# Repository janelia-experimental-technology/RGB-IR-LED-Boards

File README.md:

# RGB-IR-LED-Boards
 RGB-IR backlights 
Various LED boards that provide color and IR lighting (primarily for backlighting) in steady or pulsed modes. 
The boards are controlled by a USB-Serial command interface that provides a wide variety of opearting modes.
The 5x5 single color and RGB Combined Color have been depracated and are for reference only. 
The cuurent boards have LED areas of 5" x 5" or 7" x 7" and use separate LEDs for each color, allowing up to
three colors to be used on one board (in addition to IR). The firmware and command interace is common to all 
boards, though some features may not be available on all boards.

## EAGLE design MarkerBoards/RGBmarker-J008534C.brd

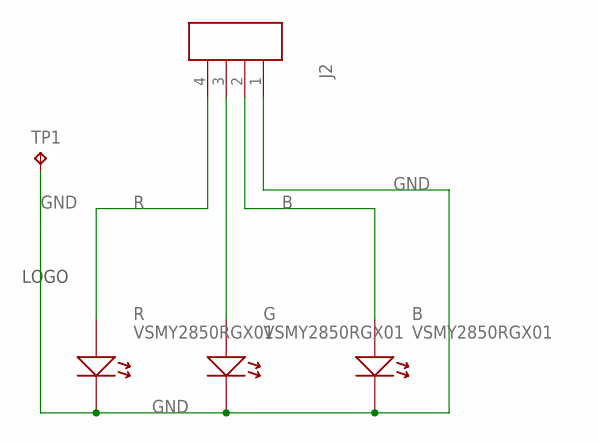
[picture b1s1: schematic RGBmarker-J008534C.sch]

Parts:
B: VSMY2850RGX01; LED_THRU_VSMY
G: VSMY2850RGX01; LED_THRU_VSMY
J2: CON4533980471; 533980471
R: VSMY2850RGX01; LED_THRU_VSMY
TP1: TPB1,27; B1,27
U$1: JFRC-LOGOLOGO_OP; LOGO_BMP_OP

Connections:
B: B.A, J2.2
GND: B.C (K), G.C (K), J2.1, R.C (K), TP1.TP
unnamed: G.A, J2.3
R: J2.4, R.A

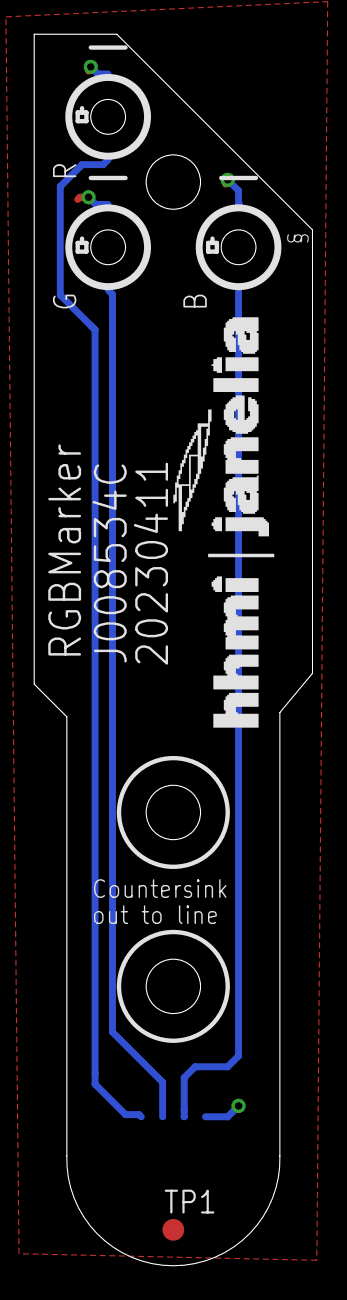
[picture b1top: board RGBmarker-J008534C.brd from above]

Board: 2 copper layers, 16.3 x 71.9 mm, 6 parts (1 on the bottom side), 4 nets.

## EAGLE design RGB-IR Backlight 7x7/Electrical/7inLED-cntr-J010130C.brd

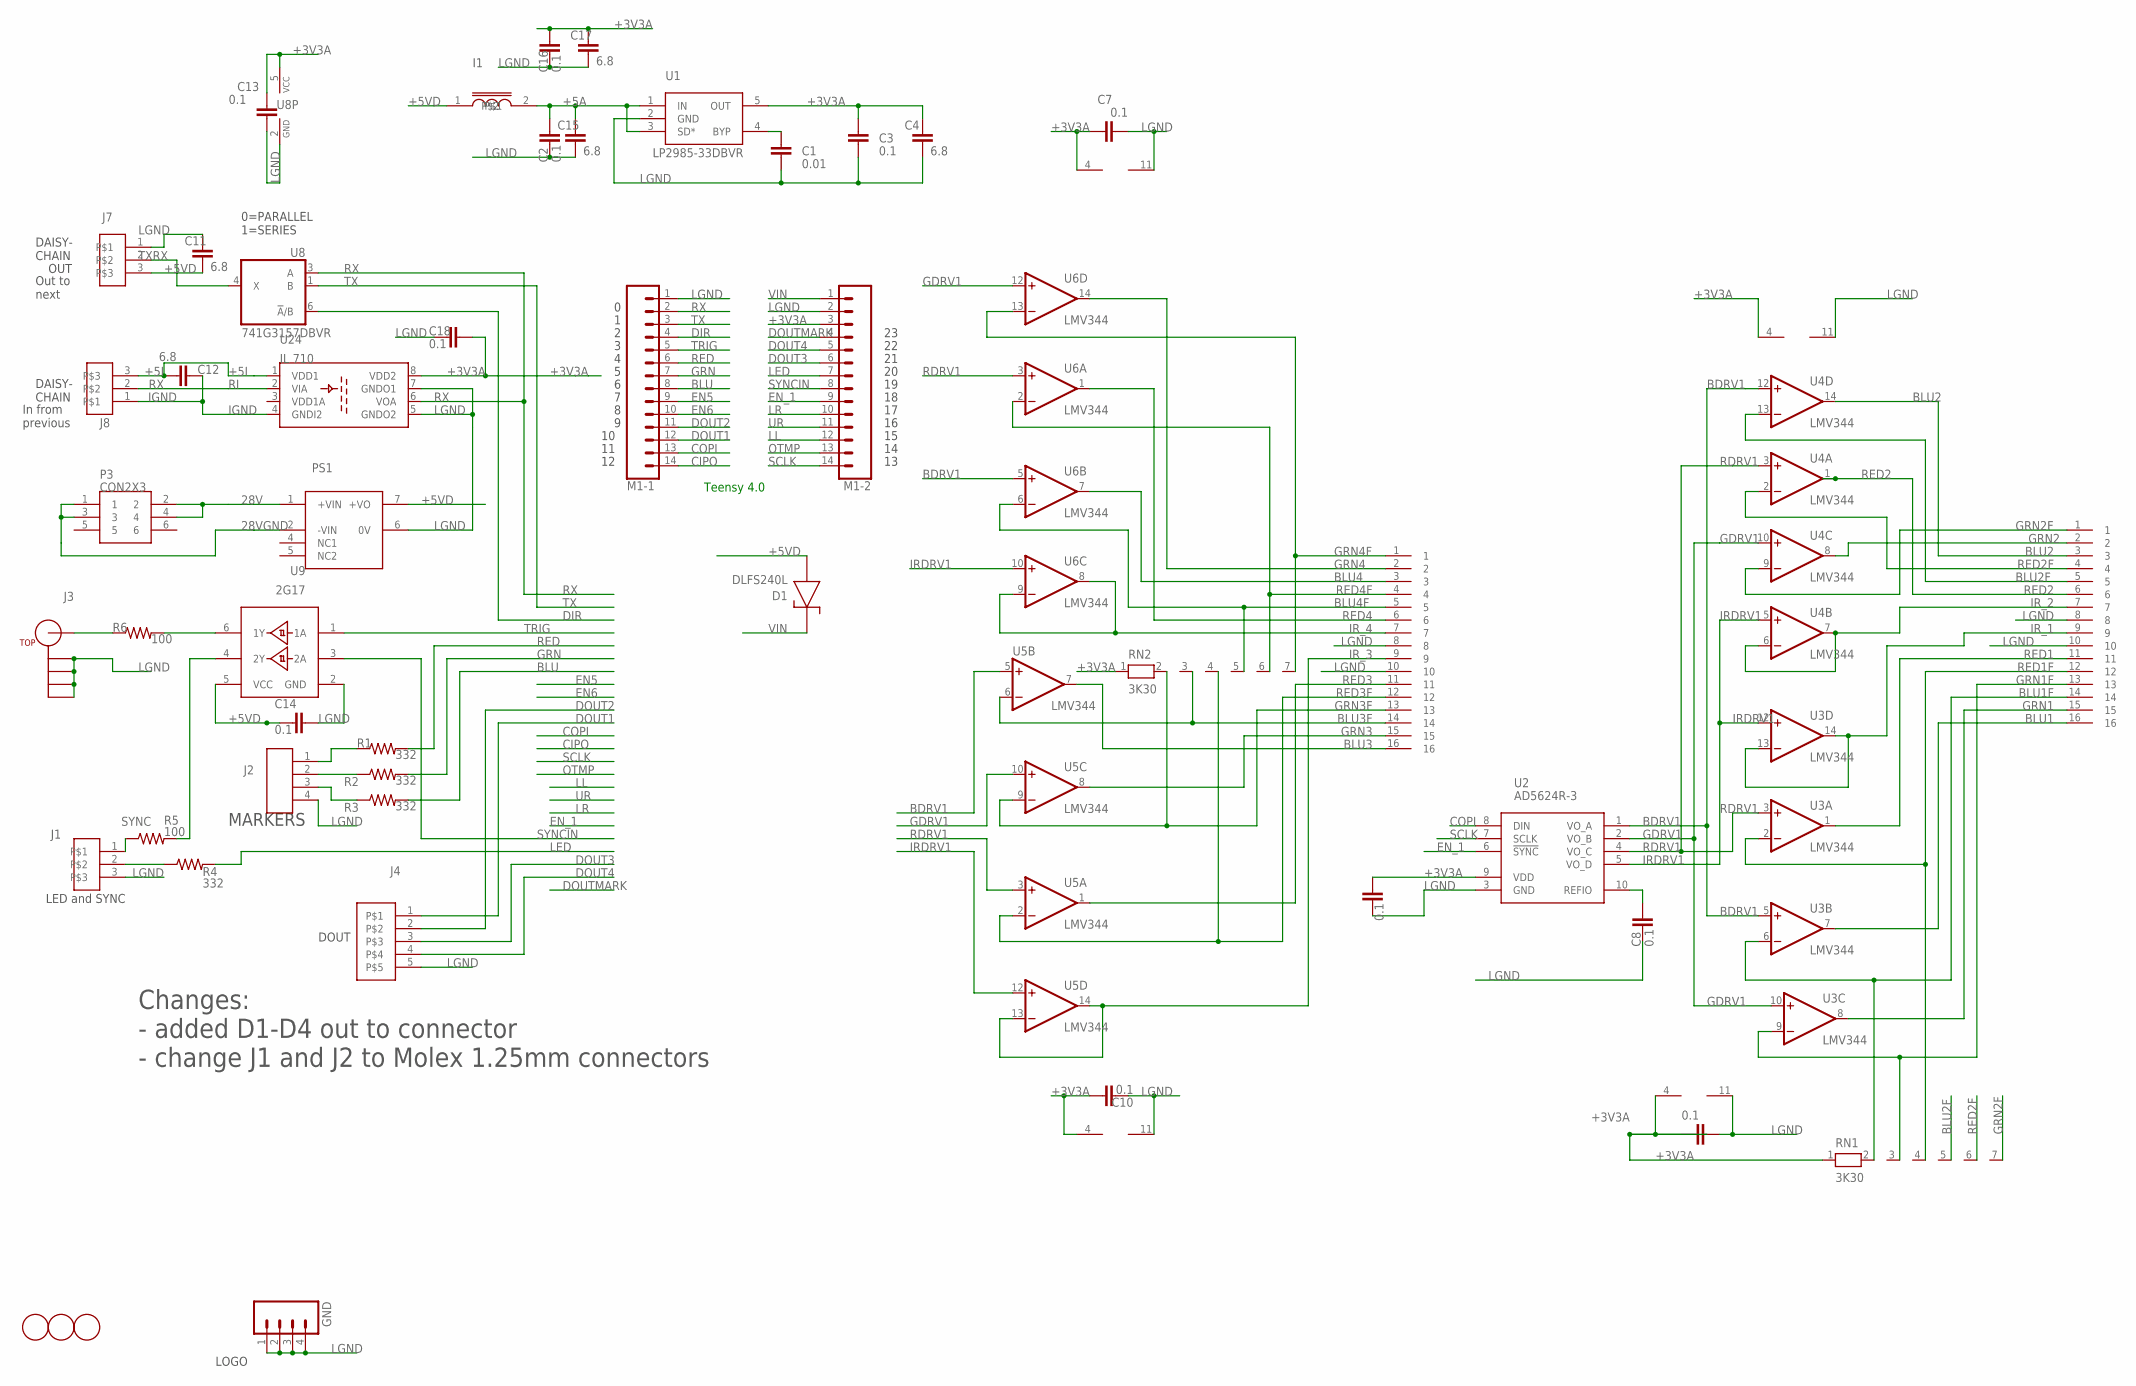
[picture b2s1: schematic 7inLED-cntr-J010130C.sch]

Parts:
C1: 0.01; 0805S
C2, C3, C5, C7, C8, C9, C10, C13, C14, C16, C18: 0.1; 0603S
C4, C15, C17: 6.8; 1206S
C11, C12: 6.8; 1210S
D1: DLFS240L; PWRDI-123
FID1, FID2, FID3: FIDUCIAL; FIDUCIAL_1MM
GND: M04LOCK; 1X04_LOCK
I1: INDUCTOR0805S; 0805S
J1: CON3DF13-3TH; DF13-3P-TH
J2: CON4DF13-4-TH; DF13-4-TH
J3: BNC-4PADBNC-5-1634503-1; 5-1634503-1
J4: CON5AMPMODU-5; AMPMODU-5
J7, J8: CON3AMPMODU-3; AMPMODU-3
M1-1, M1-2: CONN_14; 1X14
P1, P2: CON162X8PLUG; 2X8_PLUG
P3: CON2X3; 2X3_PLUG
PS1: DC-DCISLTDN-5W; DC-DC-TDN-5W
R1, R2, R3, R4: 332; 0805S
R5, R6: 100; 0805S
RN1, RN2: 3K30; RN-7
U1: LP2985-33DBVR; SOT23-5
U2: AD5624R-3; MSOP10
U3, U4, U5, U6: LMV344; SO14
U8: 741G3157DBVR; DBV_R-PDSO-G6
U9: 2G17; SOT23-6
U24: IL 710; MSOP08
U$2: JFRC-LOGOLOGO_OP; LOGO_BMP_OP

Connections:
28V: P3.2, P3.4, PS1.1 (+VIN)
28VGND: P3.1, P3.3, PS1.2 (-VIN)
+3V3A: C3.1, C4.1, C5.1, C7.1, C9.1, C10.1, C13.1, C16.1, C17.1, C18.1, M1-2.3, RN1.1, RN2.1, U1.5 (OUT), U2.9 (VDD), U3.4 (V+), U4.4 (V+), U5.4 (V+), U6.4 (V+), U8.5 (VCC), U24.8 (VDD2)
+5A: C2.1, C15.1, I1.2, U1.1 (IN), U1.3 (SD*)
+5I: C12.1, J8.3, U24.1 (VDD1)
+5VD: C11.2, C14.1, D1.A, I1.1, J7.3, PS1.7 (+VO), U9.5 (VCC)
BDRV1: U2.1 (VO_A), U3.5 (+IN), U4.12 (+IN), U5.5 (+IN), U6.5 (+IN)
BLU: M1-1.8, R3.2
BLU1: P1.16, U3.7 (OUT)
BLU1F: P1.14, RN1.2, U3.6 (-IN)
BLU2: P1.3, U4.14 (OUT)
BLU2F: P1.5, RN1.5, U4.13 (-IN)
BLU3: P2.16, U5.7 (OUT)
BLU3F: P2.14, RN2.3, U5.6 (-IN)
BLU4: P2.3, U6.7 (OUT)
BLU4F: P2.5, RN2.5, U6.6 (-IN)
CIPO: M1-1.14
COPI: M1-1.13, U2.8 (DIN)
DIR: M1-1.4, U8.6 (!A!/B)
DOUT1: J4.1, M1-1.12
DOUT2: J4.2, M1-1.11
DOUT3: J4.3, M1-2.6
DOUT4: J4.4, M1-2.5
DOUTMARK: M1-2.4
EN5: M1-1.9
EN6: M1-1.10
EN_1: M1-2.9, U2.6 (!SYNC)
GDRV1: U2.2 (VO_B), U3.10 (+IN), U4.10 (+IN), U5.10 (+IN), U6.12 (+IN)
GRN: M1-1.7, R2.2
GRN1: P1.15, U3.8 (OUT)
GRN1F: P1.13, RN1.3, U3.9 (-IN)
GRN2: P1.2, U4.8 (OUT)
GRN2F: P1.1, RN1.7, U4.9 (-IN)
GRN3: P2.15, U5.8 (OUT)
GRN3F: P2.13, RN2.2, U5.9 (-IN)
GRN4: P2.2, U6.14 (OUT)
GRN4F: P2.1, RN2.7, U6.13 (-IN)
IGND: C12.2, J8.1, U24.4 (GNDI2)
IRDRV1: U2.5 (VO_D), U3.12 (+IN), U4.5 (+IN), U5.12 (+IN), U6.10 (+IN)
IR_1: P1.9, U3.13 (-IN), U3.14 (OUT)
IR_2: P1.7, U4.6 (-IN), U4.7 (OUT)
IR_3: P2.9, U5.13 (-IN), U5.14 (OUT)
IR_4: P2.7, U6.8 (OUT), U6.9 (-IN)
LED: M1-2.7, R4.2
LGND: C1.2, C2.2, C3.2, C4.2, C5.2, C7.2, C8.2, C9.2, C10.2, C11.1, C13.2, C14.2, C15.2, C16.2, C17.2, C18.2, GND.1, GND.2, GND.3, GND.4, J1.3, J2.4, J3.2A (S1), J3.2B (S2), J3.2C (S3), J3.2D (S4), J4.5, J7.1, M1-1.1, M1-2.2, P1.8, P1.10, P2.8, P2.10, PS1.6 (0V), U1.2 (GND), U2.3 (GND), U3.11 (V-), U4.11 (V-), U5.11 (V-), U6.11 (V-), U8.2 (GND), U9.2 (GND), U24.5 (GNDO2), U24.7 (GNDO1)
LL: M1-2.12
LR: M1-2.10
unnamed: R6.2, U9.6 (1Y)
unnamed: R5.2, U9.4 (2Y)
unnamed: J2.3, R3.1
unnamed: C8.1, U2.10 (REFIO)
unnamed: C1.1, U1.4 (BYP)
unnamed: J2.2, R2.1
unnamed: J2.1, R1.1
unnamed: J3.1 (C), R6.1
unnamed: J1.2, R4.1
OTMP: M1-2.13
RDRV1: U2.4 (VO_C), U3.3 (+IN), U4.3 (+IN), U5.3 (+IN), U6.3 (+IN)
RED: M1-1.6, R1.2
RED1: P1.11, U3.1 (OUT)
RED1F: P1.12, RN1.4, U3.2 (-IN)
RED2: P1.6, U4.1 (OUT)
RED2F: P1.4, RN1.6, U4.2 (-IN)
RED3: P2.11, U5.1 (OUT)
RED3F: P2.12, RN2.4, U5.2 (-IN)
RED4: P2.6, U6.1 (OUT)
RED4F: P2.4, RN2.6, U6.2 (-IN)
RI: J8.2, U24.2 (VIA)
RX: M1-1.2, U8.3 (A), U24.6 (VOA)
SCLK: M1-2.14, U2.7 (SCLK)
SYNC: J1.1, R5.1
SYNCIN: M1-2.8, U9.3 (2A)
TRIG: M1-1.5, U9.1 (1A)
TX: M1-1.3, U8.1 (B)
TXRX: J7.2, U8.4 (X)
UR: M1-2.11
VIN: D1.K, M1-2.1

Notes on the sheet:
LED and SYNC
0=PARALLEL 1=SERIES
DAISY- CHAIN
In from previous
Out to next
OUT
MARKERS
Changes: - added D1-D4 out to connector - change J1 and J2 to Molex 1.25mm connectors
DOUT
Teensy 4.0

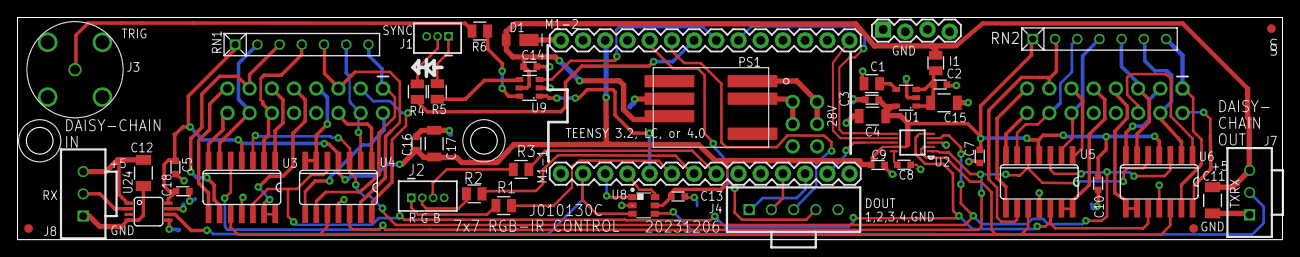
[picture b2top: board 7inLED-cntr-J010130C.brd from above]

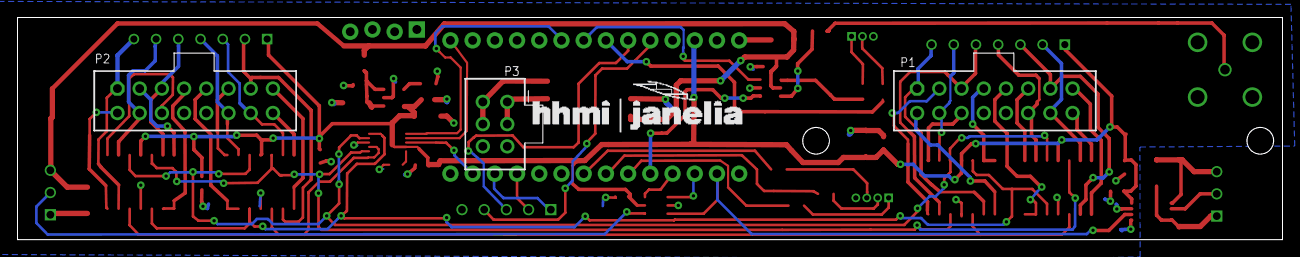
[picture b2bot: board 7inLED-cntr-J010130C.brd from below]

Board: 2 copper layers, 144.7 x 25.4 mm, 55 parts (4 on the bottom side), 69 nets.

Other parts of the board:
S1, S8: SCREW; 4-40SOCKET

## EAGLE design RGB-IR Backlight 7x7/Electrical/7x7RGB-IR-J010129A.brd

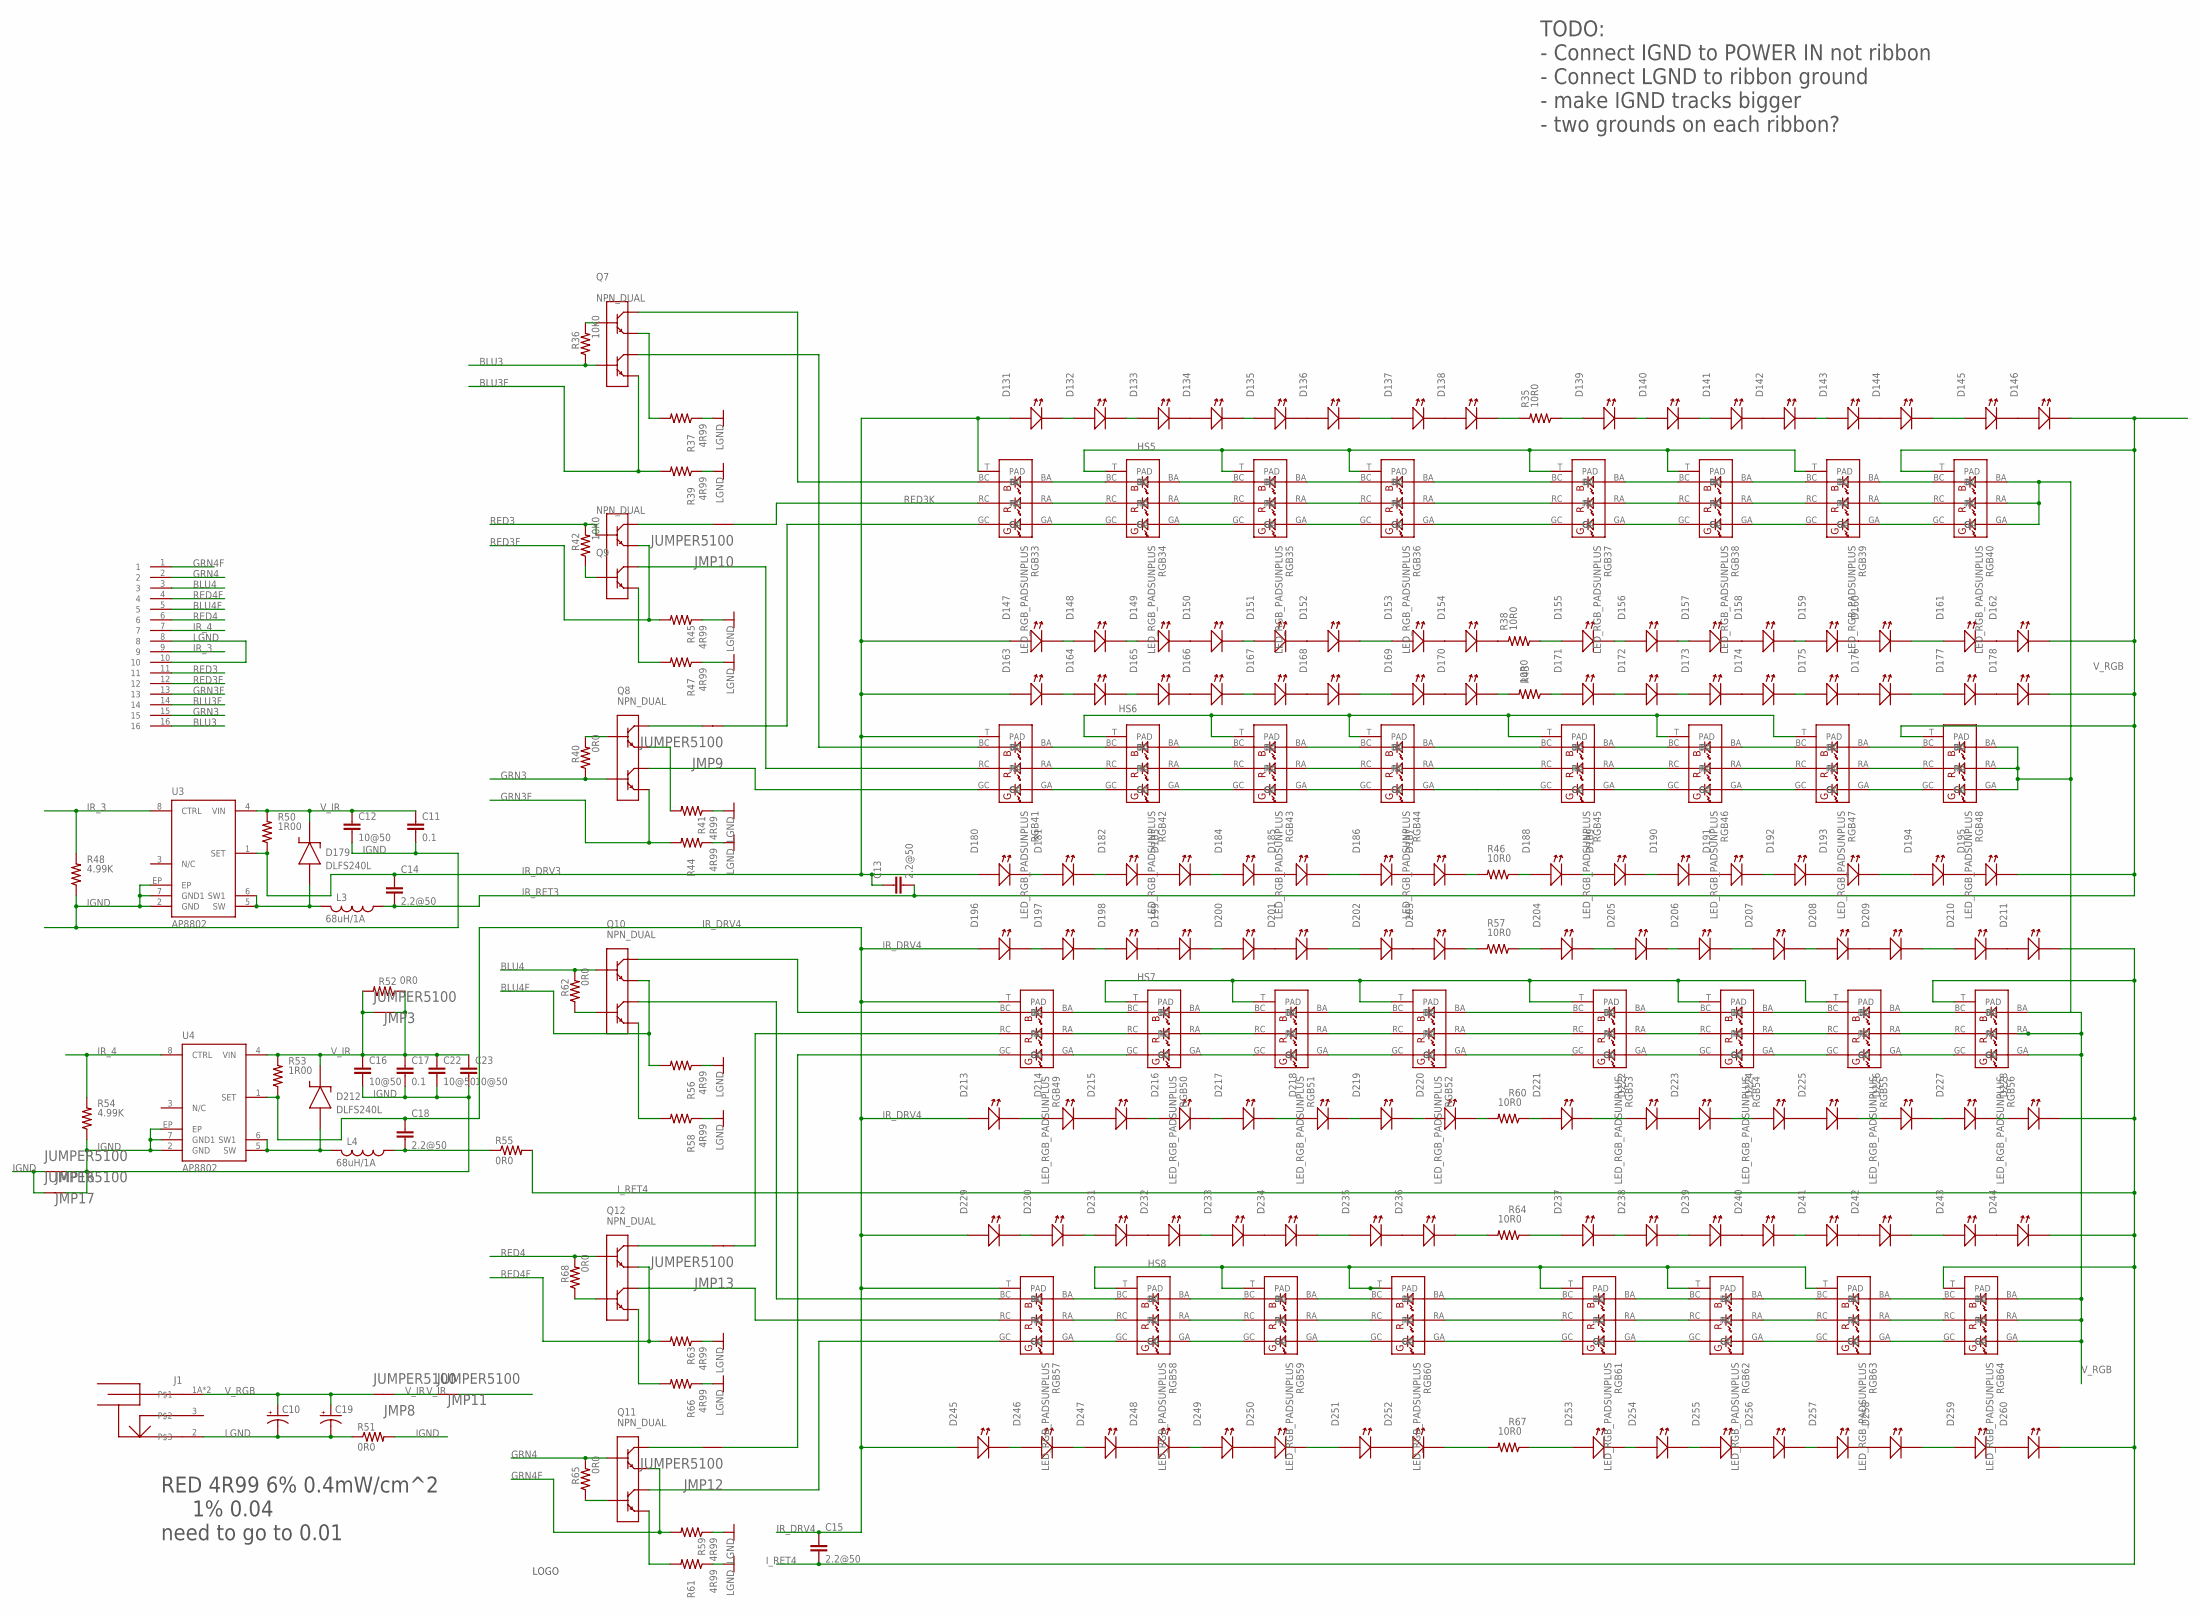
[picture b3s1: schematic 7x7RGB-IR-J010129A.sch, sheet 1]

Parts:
C10, C19: CPOL-US153CLV-0810; 153CLV-0810
C11, C17: 0.1; 0805S
C12, C16, C22, C23: 10@50; 1210S
C13, C14, C15, C18: 2.2@50; 1206S
D131, D132, D133, D134, D135, D136, D137, D138, D139, D140, D141, D142, D143, D144, D145, D146, D147, D148, D149, D150, D151, D152, D153, D154, D155, D156, D157, D158, D159, D160, D161, D162, D163, D164, D165, D166, D167, D168, D169, D170, D171, D172, D173, D174, D175, D176, D177, D178, D180, D181, D182, D183, D184, D185, D186, D187, D188, D189, D190, D191, D192, D193, D194, D195, D196, D197, D198, D199, D200, D201, D202, D203, D204, D205, D206, D207, D208, D209, D210, D211, D213, D214, D215, D216, D217, D218, D219, D220, D221, D222, D223, D224, D225, D226, D227, D228, D229, D230, D231, D232, D233, D234, D235, D236, D237, D238, D239, D240, D241, D242, D243, D244, D245, D246, D247, D248, D249, D250, D251, D252, D253, D254, D255, D256, D257, D258, D259, D260: LEDLED_SFH4050; LED_SFH4050
D179, D212: DLFS240L; PWRDI-123
J1: POWER_JACK_SHUNTPJ-002; PJ-002
JMP3, JMP8, JMP9, JMP10, JMP11, JMP12, JMP13, JMP16, JMP17: JUMPER5100; 5100
L3, L4: 68uH/1A; SRU8043
P2: CON162X8SM-SMALL; HEADER2X8_SM_SMALL
Q7, Q8, Q9, Q10, Q11, Q12: NPN_DUAL; LFPAK56D
R35, R38, R43, R46, R57, R60, R64, R67: 10R0; 1206S
R36, R42: 10K0; 1206S
R37, R39, R41, R44, R45, R47, R56, R58, R59, R61, R63, R66: 4R99; R2512
R40, R51, R55, R62, R65, R68: 0R0; 1206S
R48, R54: 4.99K; 0805S
R50, R53: 1R00; 1206S
R52: 0R0; R1206
RGB33, RGB34, RGB35, RGB36, RGB37, RGB38, RGB39, RGB40, RGB41, RGB42, RGB43, RGB44, RGB45, RGB46, RGB47, RGB48, RGB49, RGB50, RGB51, RGB52, RGB53, RGB54, RGB55, RGB56, RGB57, RGB58, RGB59, RGB60, RGB61, RGB62, RGB63, RGB64: LED_RGB_PADSUNPLUS; SUNPLUS_RGB
U3, U4: AP8802; SOIC8-EP
U$19: JFRC-LOGOLOGO_OP; LOGO_BMP_OP

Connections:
BLU3: P2.16, Q7.4 (B2), R36.1
BLU3F: P2.14, Q7.3 (E2), R39.2
BLU3K: Q7.7 (C1), Q7.8 (C1), Q7.78 (C1), RGB33.BC
BLU4: P2.3, Q10.2 (B1), R62.2
BLU4F: P2.5, Q10.1 (E1), R56.2
G4: Q11.3 (E2), R61.2
G4A: Q11.4 (B2), R65.1
GRN3: P2.15, Q8.4 (B2), R40.1
GRN3F: P2.13, Q8.3 (E2), R44.2
GRN3K: JMP9.1, RGB33.GC
GRN4: P2.2, Q11.2 (B1), R65.2
GRN4F: P2.1, Q11.1 (E1), R59.2
GULA_1: Q11.5 (C2), Q11.6 (C2), Q11.56 (C2), RGB57.GC
GULA_2: Q12.5 (C2), Q12.6 (C2), Q12.56 (C2), RGB57.RC
GULA_3: Q8.5 (C2), Q8.6 (C2), Q8.56 (C2), RGB41.GC
GULA_4: Q9.5 (C2), Q9.6 (C2), Q9.56 (C2), RGB41.RC
HS5: RGB34.T (PAD), RGB35.T (PAD), RGB36.T (PAD), RGB37.T (PAD), RGB38.T (PAD), RGB39.T (PAD)
HS6: RGB42.T (PAD), RGB43.T (PAD), RGB44.T (PAD), RGB45.T (PAD), RGB46.T (PAD), RGB47.T (PAD)
HS7: RGB50.T (PAD), RGB51.T (PAD), RGB52.T (PAD), RGB53.T (PAD), RGB54.T (PAD), RGB55.T (PAD)
HS8: RGB58.T (PAD), RGB59.T (PAD), RGB60.T (PAD), RGB61.T (PAD), RGB62.T (PAD), RGB63.T (PAD)
IGND: C11.2, C12.2, C16.2, C17.2, C22.2, C23.2, JMP16.1, JMP16.2, JMP17.1, JMP17.2, R48.1, R51.2, R54.1, U3.2 (GND), U3.7 (GND1), U3.EP, U4.2 (GND), U4.7 (GND1), U4.EP
IR_3: P2.9, R48.2, U3.8 (CTRL)
IR_4: P2.7, R54.2, U4.8 (CTRL)
IR_DRV3: C13.1, C14.1, D131.A, D147.A, D163.A, D180.A, R50.1, RGB33.T (PAD), RGB41.T (PAD), U3.1 (SET)
IR_DRV4: C15.1, C18.1, D196.A, D213.A, D229.A, D245.A, R53.1, RGB49.T (PAD), RGB57.T (PAD), U4.1 (SET)
IR_RET3: C13.2, C14.2, D146.C (K), D162.C (K), D178.C (K), D195.C (K), L3.1, RGB40.T (PAD), RGB48.T (PAD)
I_RET4: C15.2, D211.C (K), D228.C (K), D244.C (K), D260.C (K), R55.2, RGB56.T (PAD), RGB64.T (PAD)
LGND: C10.-, C19.-, J1.2, P2.8, P2.10, R37.1, R39.1, R41.1, R44.1, R45.1, R47.1, R51.1, R56.1, R58.1, R59.1, R61.1, R63.1, R66.1; also elsewhere on the board
unnamed: D227.C (K), D228.A
unnamed: Q12.4 (B2), R68.1
unnamed: Q8.1 (E1), R41.2
unnamed: JMP12.1, RGB49.GC
unnamed: Q10.7 (C1), Q10.8 (C1), Q10.78 (C1), RGB49.BC
unnamed: Q10.5 (C2), Q10.6 (C2), Q10.56 (C2), RGB57.BC
unnamed: Q9.3 (E2), R47.2
unnamed: Q9.4 (B2), R42.1
unnamed: Q8.2 (B1), R40.2
unnamed: D139.A, R35.1
unnamed: JMP13.2, Q12.7 (C1), Q12.8 (C1), Q12.78 (C1)
unnamed: JMP12.2, Q11.7 (C1), Q11.8 (C1), Q11.78 (C1)
unnamed: D138.C (K), R35.2
unnamed: D154.C (K), R38.2
unnamed: D155.A, R38.1
unnamed: JMP13.1, RGB49.RC
unnamed: D171.A, R43.1
unnamed: D170.C (K), R43.2
unnamed: D188.A, R46.1
unnamed: D187.C (K), R46.2
unnamed: D203.C (K), R57.2
unnamed: RGB63.BA, RGB64.BC
unnamed: D212.A, L4.2, U4.5 (SW), U4.6 (SW1)
unnamed: C18.2, L4.1, R55.1
unnamed: RGB63.RA, RGB64.RC
unnamed: D204.A, R57.1
unnamed: D221.A, R60.1
unnamed: D220.C (K), R60.2
unnamed: D237.A, R64.1
unnamed: Q10.4 (B2), R62.1
unnamed: Q10.3 (E2), R58.2
unnamed: D236.C (K), R64.2
unnamed: D253.A, R67.1
unnamed: D252.C (K), R67.2
unnamed: D179.A, L3.2, U3.5 (SW), U3.6 (SW1)
unnamed: RGB47.GA, RGB48.GC
unnamed: RGB46.GA, RGB47.GC
unnamed: RGB45.GA, RGB46.GC
unnamed: RGB44.GA, RGB45.GC
unnamed: RGB43.GA, RGB44.GC
unnamed: RGB42.GA, RGB43.GC
unnamed: RGB63.GA, RGB64.GC
unnamed: RGB41.GA, RGB42.GC
unnamed: RGB47.RA, RGB48.RC
unnamed: RGB46.RA, RGB47.RC
unnamed: RGB45.RA, RGB46.RC
unnamed: RGB44.RA, RGB45.RC
unnamed: RGB43.RA, RGB44.RC
unnamed: RGB42.RA, RGB43.RC
unnamed: RGB41.RA, RGB42.RC
unnamed: RGB41.BA, RGB42.BC
unnamed: RGB42.BA, RGB43.BC
unnamed: RGB43.BA, RGB44.BC
unnamed: RGB44.BA, RGB45.BC
unnamed: RGB45.BA, RGB46.BC
unnamed: RGB46.BA, RGB47.BC
unnamed: RGB47.BA, RGB48.BC
unnamed: D181.C (K), D182.A
unnamed: D182.C (K), D183.A
unnamed: RGB33.RA, RGB34.RC
unnamed: D184.C (K), D185.A
unnamed: D186.C (K), D187.A
unnamed: D180.C (K), D181.A
unnamed: D183.C (K), D184.A
unnamed: D185.C (K), D186.A
unnamed: D189.C (K), D190.A
unnamed: D190.C (K), D191.A
unnamed: D192.C (K), D193.A
unnamed: D194.C (K), D195.A
unnamed: D188.C (K), D189.A
unnamed: D191.C (K), D192.A
unnamed: D193.C (K), D194.A
unnamed: D164.C (K), D165.A
unnamed: D165.C (K), D166.A
unnamed: D167.C (K), D168.A
unnamed: D169.C (K), D170.A
unnamed: D163.C (K), D164.A
unnamed: D166.C (K), D167.A
unnamed: D168.C (K), D169.A
unnamed: D172.C (K), D173.A
unnamed: D173.C (K), D174.A
unnamed: D175.C (K), D176.A
unnamed: D177.C (K), D178.A
unnamed: D171.C (K), D172.A
unnamed: D174.C (K), D175.A
unnamed: D176.C (K), D177.A
unnamed: RGB55.GA, RGB56.GC
unnamed: RGB54.GA, RGB55.GC
unnamed: RGB53.GA, RGB54.GC
unnamed: RGB52.GA, RGB53.GC
unnamed: RGB51.GA, RGB52.GC
unnamed: RGB50.GA, RGB51.GC
unnamed: RGB49.GA, RGB50.GC
unnamed: RGB55.RA, RGB56.RC
unnamed: RGB54.RA, RGB55.RC
unnamed: RGB53.RA, RGB54.RC
unnamed: RGB52.RA, RGB53.RC
unnamed: RGB51.RA, RGB52.RC
unnamed: RGB50.RA, RGB51.RC
unnamed: RGB49.RA, RGB50.RC
unnamed: RGB49.BA, RGB50.BC
unnamed: RGB50.BA, RGB51.BC
unnamed: RGB51.BA, RGB52.BC
unnamed: RGB52.BA, RGB53.BC
unnamed: RGB53.BA, RGB54.BC
unnamed: RGB54.BA, RGB55.BC
unnamed: RGB55.BA, RGB56.BC
unnamed: D197.C (K), D198.A
unnamed: D198.C (K), D199.A
unnamed: D200.C (K), D201.A
unnamed: D202.C (K), D203.A
unnamed: D196.C (K), D197.A
unnamed: D199.C (K), D200.A
unnamed: D201.C (K), D202.A
unnamed: D205.C (K), D206.A
unnamed: D206.C (K), D207.A
unnamed: D208.C (K), D209.A
unnamed: D210.C (K), D211.A
unnamed: D204.C (K), D205.A
unnamed: D207.C (K), D208.A
unnamed: D209.C (K), D210.A
unnamed: D214.C (K), D215.A
unnamed: D215.C (K), D216.A
unnamed: D217.C (K), D218.A
unnamed: D219.C (K), D220.A
unnamed: D213.C (K), D214.A
unnamed: D216.C (K), D217.A
unnamed: D218.C (K), D219.A
unnamed: D222.C (K), D223.A
unnamed: D224.C (K), D225.A
unnamed: D226.C (K), D227.A
unnamed: D221.C (K), D222.A
unnamed: D223.C (K), D224.A
unnamed: D225.C (K), D226.A
unnamed: RGB39.GA, RGB40.GC
unnamed: RGB38.GA, RGB39.GC
unnamed: RGB37.GA, RGB38.GC
unnamed: RGB36.GA, RGB37.GC
unnamed: RGB35.GA, RGB36.GC
unnamed: RGB34.GA, RGB35.GC
unnamed: RGB33.GA, RGB34.GC
unnamed: RGB39.RA, RGB40.RC
unnamed: RGB38.RA, RGB39.RC
unnamed: RGB37.RA, RGB38.RC
unnamed: RGB36.RA, RGB37.RC
unnamed: RGB35.RA, RGB36.RC
unnamed: RGB34.RA, RGB35.RC
unnamed: RGB33.BA, RGB34.BC
unnamed: RGB34.BA, RGB35.BC
unnamed: RGB35.BA, RGB36.BC
unnamed: RGB36.BA, RGB37.BC
unnamed: RGB37.BA, RGB38.BC
unnamed: RGB38.BA, RGB39.BC
unnamed: RGB39.BA, RGB40.BC
unnamed: D132.C (K), D133.A
unnamed: D133.C (K), D134.A
unnamed: D135.C (K), D136.A
unnamed: D137.C (K), D138.A
unnamed: D131.C (K), D132.A
unnamed: D134.C (K), D135.A
unnamed: D136.C (K), D137.A
unnamed: D140.C (K), D141.A
unnamed: D141.C (K), D142.A
unnamed: D143.C (K), D144.A
unnamed: D145.C (K), D146.A
unnamed: D139.C (K), D140.A
unnamed: D142.C (K), D143.A
unnamed: D144.C (K), D145.A
unnamed: D148.C (K), D149.A
unnamed: D149.C (K), D150.A
unnamed: D151.C (K), D152.A
unnamed: D153.C (K), D154.A
unnamed: D147.C (K), D148.A
unnamed: D150.C (K), D151.A
unnamed: D152.C (K), D153.A
unnamed: D156.C (K), D157.A
unnamed: D157.C (K), D158.A
unnamed: D159.C (K), D160.A
unnamed: D161.C (K), D162.A
unnamed: D155.C (K), D156.A
unnamed: D158.C (K), D159.A
unnamed: D160.C (K), D161.A
unnamed: Q7.1 (E1), R37.2
unnamed: Q7.5 (C2), Q7.6 (C2), Q7.56 (C2), RGB41.BC
unnamed: RGB62.GA, RGB63.GC
unnamed: RGB61.GA, RGB62.GC
unnamed: RGB60.GA, RGB61.GC
unnamed: RGB59.GA, RGB60.GC
unnamed: RGB58.GA, RGB59.GC
unnamed: RGB57.GA, RGB58.GC
unnamed: RGB62.RA, RGB63.RC
unnamed: RGB61.RA, RGB62.RC
unnamed: RGB60.RA, RGB61.RC
unnamed: RGB59.RA, RGB60.RC
unnamed: RGB58.RA, RGB59.RC
unnamed: RGB57.RA, RGB58.RC
unnamed: RGB57.BA, RGB58.BC
unnamed: RGB58.BA, RGB59.BC
unnamed: RGB59.BA, RGB60.BC
unnamed: RGB60.BA, RGB61.BC
unnamed: RGB61.BA, RGB62.BC
unnamed: RGB62.BA, RGB63.BC
unnamed: D230.C (K), D231.A
unnamed: D231.C (K), D232.A
unnamed: D233.C (K), D234.A
unnamed: D235.C (K), D236.A
unnamed: D229.C (K), D230.A
unnamed: D232.C (K), D233.A
unnamed: D234.C (K), D235.A
unnamed: D238.C (K), D239.A
unnamed: D239.C (K), D240.A
unnamed: D241.C (K), D242.A
unnamed: D243.C (K), D244.A
unnamed: D237.C (K), D238.A
unnamed: D240.C (K), D241.A
unnamed: D242.C (K), D243.A
unnamed: D246.C (K), D247.A
unnamed: D247.C (K), D248.A
unnamed: D249.C (K), D250.A
unnamed: D251.C (K), D252.A
unnamed: D245.C (K), D246.A
unnamed: D248.C (K), D249.A
unnamed: D250.C (K), D251.A
unnamed: D254.C (K), D255.A
unnamed: D255.C (K), D256.A
unnamed: D257.C (K), D258.A
unnamed: D259.C (K), D260.A
unnamed: D253.C (K), D254.A
unnamed: D256.C (K), D257.A
unnamed: D258.C (K), D259.A
unnamed: JMP10.2, Q9.7 (C1), Q9.8 (C1), Q9.78 (C1)
unnamed: JMP9.2, Q8.7 (C1), Q8.8 (C1), Q8.78 (C1)
unnamed: Q7.2 (B1), R36.2
R4: Q12.3 (E2), R66.2
RED3: P2.11, Q9.2 (B1), R42.2
RED3F: P2.12, Q9.1 (E1), R45.2
RED3K: JMP10.1, RGB33.RC
RED4: P2.6, Q12.2 (B1), R68.2
RED4F: P2.4, Q12.1 (E1), R63.2
V_IR: C11.1, C12.1, C16.1, C17.1, C22.1, C23.1, D179.K, D212.K, JMP3.1, JMP3.2, JMP8.2, JMP11.1, JMP11.2, R50.2, R52.1, R52.2, R53.2, U3.4 (VIN), U4.4 (VIN)
V_RGB: C10.+, C19.+, J1.1A, J1.1B, JMP8.1, RGB40.BA, RGB40.GA, RGB40.RA, RGB48.BA, RGB48.GA, RGB48.RA, RGB56.BA, RGB56.GA, RGB56.RA, RGB64.BA, RGB64.GA, RGB64.RA; also elsewhere on the board

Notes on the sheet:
RED 4R99 6% 0.4mW/cm^2 1% 0.04 need to go to 0.01
TODO: - Connect IGND to POWER IN not ribbon - Connect LGND to ribbon ground - make IGND tracks bigger - two grounds on each ribbon?

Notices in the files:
parts and their libraries:
SparkFun: Licensing: CC v3.0 Share-Alike You are welcome to use this library for commercial purposes.
SparkFun-Connectors: Licensing: Creative Commons ShareAlike 4.0 International - https://creativecommons.org/licenses/by-sa/4.0
